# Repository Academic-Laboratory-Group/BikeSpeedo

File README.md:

# BikeSpeedo
Bicycle speedometer. Project for Sensors In Embedded Systems, Electronics and Telecommunications, master's studies at University of Science and Technology in Cracow. Classes are led in Polish so description and files from this place will be too, except code and other source files.

## Cel projektu
Celem projektu jest skonstruowanie modułu prędkościomierza rowerowego do płytki Nucleo. Należy zaprojektować płytkę PCB oraz oprogramowanie. Ważną cechą projektu ma być przystępna cena gotowego produktu mimo zainstalowanych w nim udogodnień (wyświetlacz dotykowy, zasilanie bateryjne). Projekt ma być możliwy do użycia w celach edukacyjnych, a więc zaprojektowany tak, żeby dało się łatwo zrozumieć zastosowane w nim rozwiązania.

## Podział obowiązków
Nad częścią hardware-ową główny nadzór będzie sprawował Krzysztof, natomiast nad software-ową Norbert. Oczywiście w projekcie przewidziana jest ciągła współpraca, co powinno być widoczne na koniec w postaci przeplatających się commitów obu członków.

## Założenia projektowe
* Pomiar prędkości przy pomocy czujnika Halla na podstawie liczby obrotów koła.
* Konfiguracja oraz prezentacja wyników na wyświetlaczu dotykowym.
* Urządzenie zasilane z akumulatora (z pełną jego obsługą, czyli ładowarką + monitoringiem stanu naładowania).
* Projekt płytki PCB w celu demonstracji urządzenia.
* Szacowany czas pracy na baterii Li-Ion o pojemności 1300 mAh powinien wynieść około 7.5 godziny.

## Efekt

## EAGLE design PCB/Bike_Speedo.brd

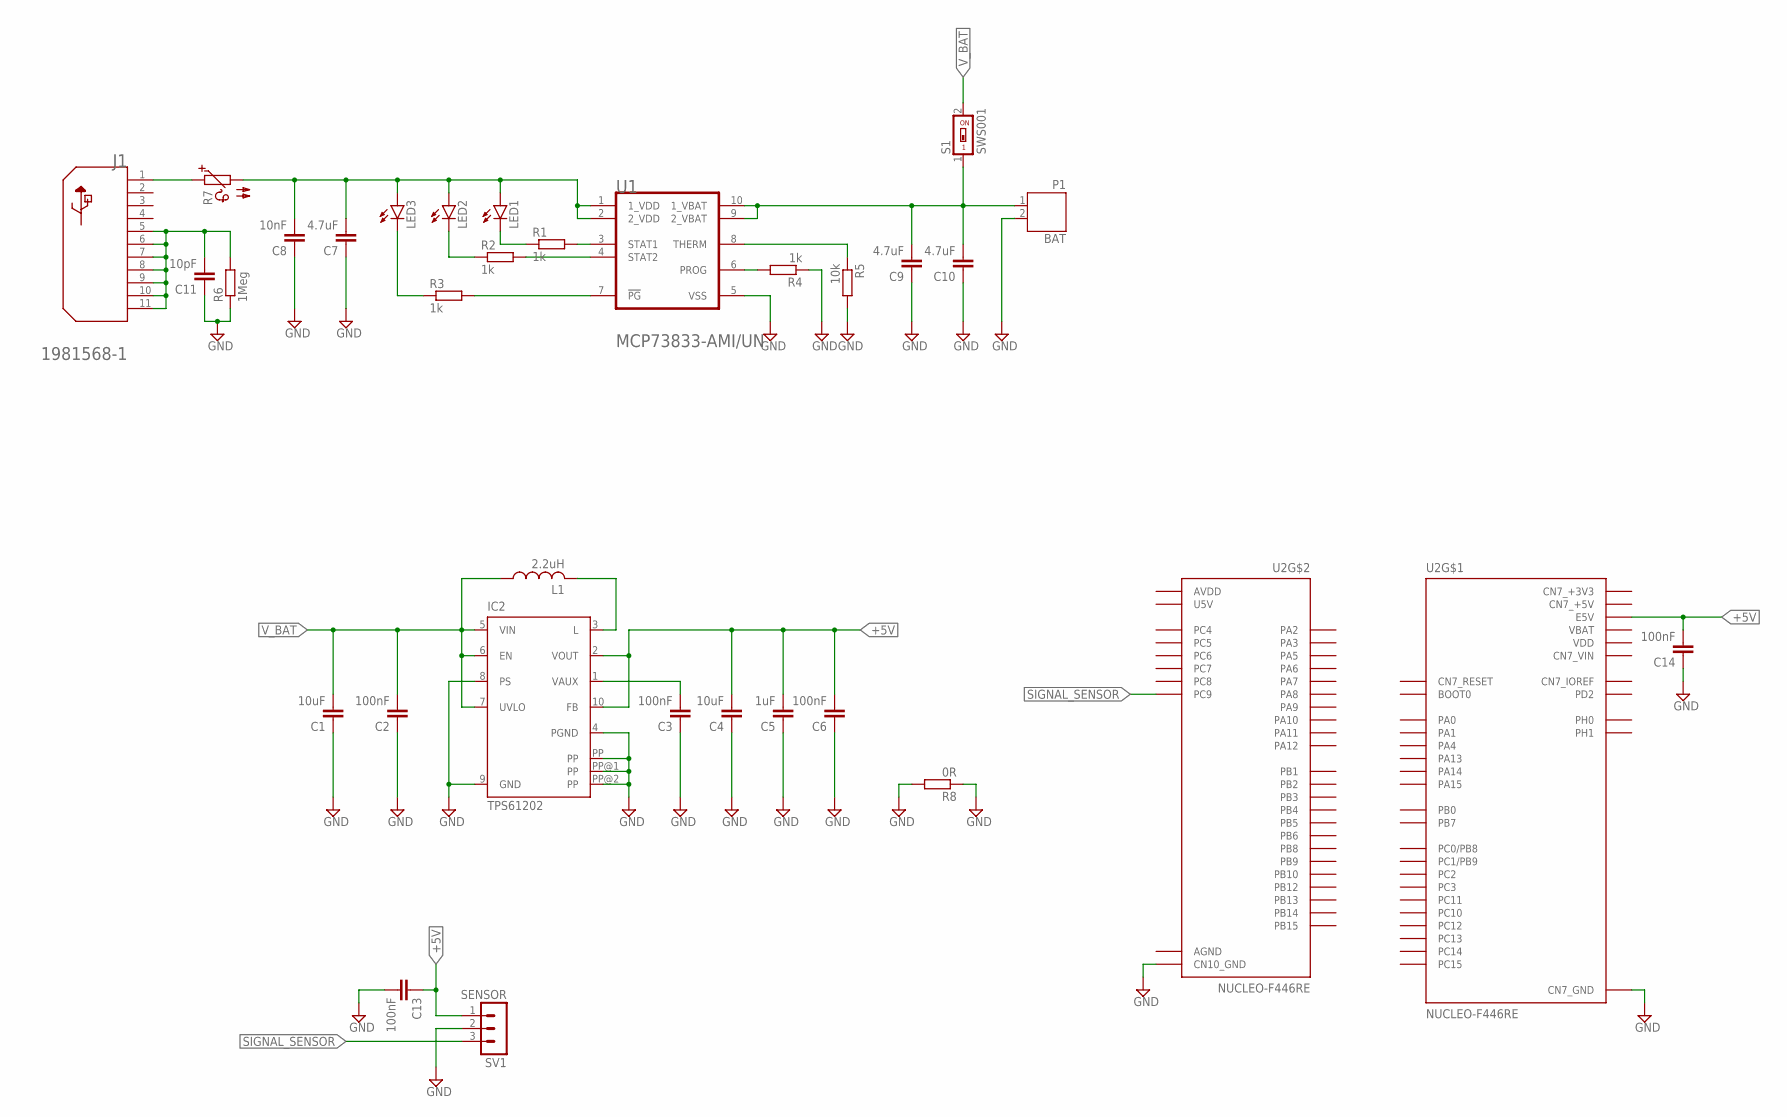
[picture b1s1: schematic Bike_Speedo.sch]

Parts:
C1, C4: 10uF; C0805
C2, C3, C6, C13, C14: 100nF; C0805
C5: 1uF; C0805
C7, C9, C10: 4.7uF; C0805
C8: 10nF; C0805
C11: 10pF; C0805
IC2: TPS61202; S-PDSO-N10
J1: TE_CONNECTIVITY_1981568-1TE_CONNECTIVITY_1981568-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; TE_CONNECTIVITY_1981568-1_0
L1: 2.2uH; L3216C
LED1, LED2, LED3: LEDSML0805; SML0805
P1: BAT; JST-PH2
R1, R2, R3, R4: 1k; R0805
R5: 10k; R0805
R6: 1Meg; R0805
R7: PTC660; P660
R8: 0R; R0805
S1: SWS001; SMS-001
SV1: SENSOR; MA03-1
U1: MICROCHIP_MCP73833-AMI-UNMICROCHIP_MCP73833-AMI-U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; MICROCHIP_MCP73833-AMI-UN_0
U2: NUCLEO-F446RE; MODULE_NUCLEO-F446RE

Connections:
+5V: C4.2, C5.2, C6.2, C13.1, C14.2, IC2.2 (VOUT), IC2.10 (FB), SV1.1, U2.CN7_6 (E5V)
AGND: U2.CN10_32 (AGND)
AREF: U2.CN5_8 (AREF)
AVDD: U2.CN10_7 (AVDD)
CN5_GND: U2.CN5_7 (CN5_GND)
CN6_+3V3: U2.CN6_4 (CN6_+3V3)
CN6_+5V: U2.CN6_5 (CN6_+5V)
CN6_GND: U2.CN6_6 (CN6_GND), U2.CN6_7 (CN6_GND)
CN6_VIN: U2.CN6_8 (CN6_VIN)
CN7_+3V3: U2.CN7_16 (CN7_+3V3)
CN7_+5V: U2.CN7_18 (CN7_+5V)
CN7_VIN: U2.CN7_24 (CN7_VIN)
GND: C1.1, C2.1, C3.1, C4.1, C5.1, C6.1, C7.1, C8.1, C9.1, C10.1, C11.1, C13.2, C14.1, IC2.4 (PGND), IC2.8 (PS), IC2.9 (GND), IC2.PP, IC2.PP@1 (PP), IC2.PP@2 (PP), P1.2, R4.1, R5.2, R6.1, R8.1, R8.2, SV1.2, U1.5 (VSS), U2.CN7_8 (CN7_GND), U2.CN7_19 (CN7_GND), U2.CN7_20 (CN7_GND), U2.CN7_22 (CN7_GND), U2.CN10_9 (CN10_GND), U2.CN10_20 (CN10_GND)
unnamed: J1.1 (VBUS), R7.1
unnamed: IC2.3 (L), L1.2
unnamed: C3.2, IC2.1 (VAUX)
unnamed: C7.2, C8.2, LED1.A, LED2.A, LED3.A, R7.2, U1.1 (1_VDD), U1.2 (2_VDD)
unnamed: C11.2, J1.5 (GND), J1.6 (SHLD1), J1.7 (SHLD2), J1.8 (SHLD3), J1.9 (SHLD4), J1.10 (SHLD5), J1.11 (SHLD6), R6.2
unnamed: LED1.C, R1.1
unnamed: LED2.C, R2.1
unnamed: LED3.C, R3.1
unnamed: R3.2, U1.7 (!PG!)
unnamed: R2.2, U1.4 (STAT2)
unnamed: R1.2, U1.3 (STAT1)
unnamed: R4.2, U1.6 (PROG)
unnamed: R5.1, U1.8 (THERM)
unnamed: C9.2, C10.2, P1.1, S1.1, U1.9 (2_VBAT), U1.10 (1_VBAT)
SIGNAL_SENSOR: SV1.3, U2.CN10_1 (PC9)
U5V: U2.CN10_8 (U5V)
VBAT: U2.CN7_33 (VBAT)
VDD: U2.CN7_5 (VDD)
V_BAT: C1.2, C2.2, IC2.5 (VIN), IC2.6 (EN), IC2.7 (UVLO), L1.1, S1.2

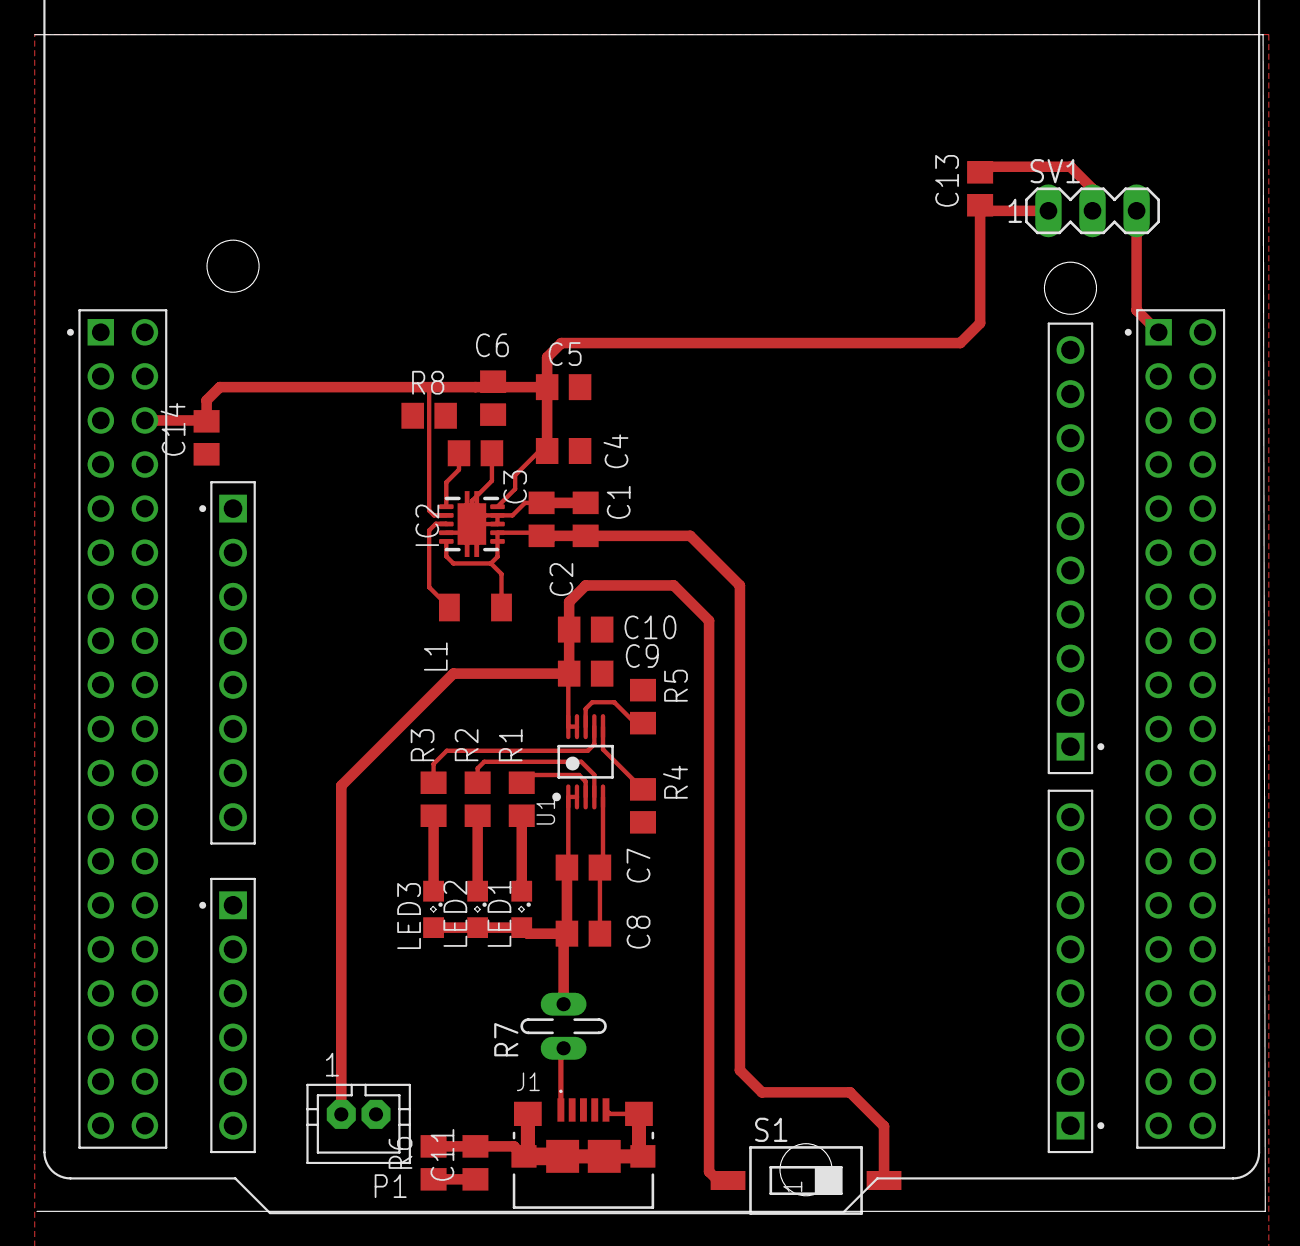
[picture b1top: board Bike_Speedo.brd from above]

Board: 2 copper layers, 70.9 x 67.8 mm, 32 parts (0 on the bottom side), 19 nets.

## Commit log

2021-03-13 Readme photo
2021-03-13 Add presentation
2021-03-14 Update presentation
2021-03-16 Add code for screen
2021-03-17 Add cod for sensor
2021-03-17 Presentation v.2
2021-03-22 New pdf version + updated gitignore
2021-03-22 Add prototype schematic
2021-03-27 Refactoring
2021-04-12 Update schematic
2021-05-06 Update code
2021-05-09 refactor
2021-05-11 fixed crazy velocities
2021-05-12 update PCB
2021-05-13 modified PCB
2021-06-01 Update schematic and board
2021-06-01 Add raport
2021-06-02 movie
2021-06-07 Corect raport
